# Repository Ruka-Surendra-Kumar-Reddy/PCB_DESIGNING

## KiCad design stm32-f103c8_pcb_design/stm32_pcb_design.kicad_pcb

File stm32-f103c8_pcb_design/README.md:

THIS FILE CONTAINS THE FOLLOWING :-  

schematic file of stm32f103c8  
board layout of stm32f103c8  
gerbers  
components list

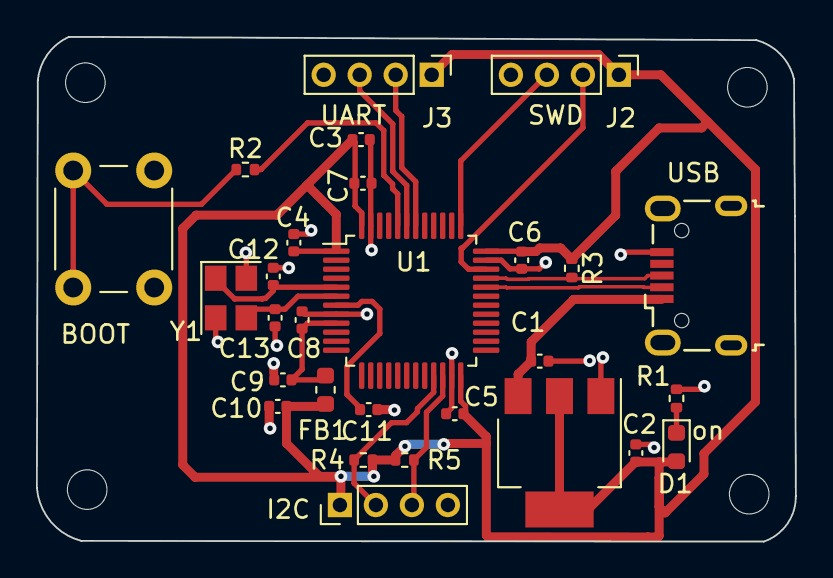
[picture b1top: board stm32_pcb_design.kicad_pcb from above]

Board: 2 copper layers, 42.2 x 28.0 mm, 32 parts (0 on the bottom side), 18 nets.

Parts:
C1, C2: 22u; C_0402_1005Metric
C3, C8: 10u; C_0402_1005Metric
C4, C5, C6, C7, C11: 100n; C_0402_1005Metric
C9, C10: 1u; C_0402_1005Metric
C12, C13: 10p; C_0402_1005Metric
D1: RED; LED_0603_1608Metric
FB1: 120R; L_0603_1608Metric
H1, H2, H3, H4: MountingHole; MountingHole_2.2mm_M2
J1: USB_B_Micro; USB_Micro-B_Wuerth_629105150521
J2, J3, J4: Conn_01x04_Pin; PinHeader_1x04_P2.00mm_Vertical
R1, R3, R4, R5: 1k5; R_0402_1005Metric
R2: 10k; R_0402_1005Metric
SW1: SW_SPDT; SW_PUSH_6mm
U1: STM32F103C8; LQFP-48_7x7mm_P0.5mm
U2: AMS1117-3.3; SOT-223-3_TabPin2
Y1: 16MHZ; Crystal_SMD_3225-4Pin_3.2x2.5mm

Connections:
+3.3V: C2.1, C3.1, C4.1, C5.1, C6.1, C7.1, C10.1, D1.2 (A), FB1.2, J2.1, J3.1, J4.1, R3.1, R4.1, R5.1, U1.1 (VBAT), U1.24 (VDD), U1.36 (VDD), U1.48 (VDD), U2.2 (VO)
+3.3VA: C8.1, C9.1, FB1.1, U1.9 (VDDA)
/BOOTO: R2.2, U1.44 (BOOT0)
/HSE_IN: C12.1, U1.5 (PD0), Y1.1
/HSE_OUT: C13.1, U1.6 (PD1), Y1.3
/I2C_SCL: J4.2, R4.2, U1.21 (PB10)
/I2C_SDA: J4.3, R5.2, U1.22 (PB11)
/NRST: C11.1, U1.7 (NRST)
/PWR_LED_K: D1.1 (K), R1.1
/SWCLK: J2.3, U1.37 (PA14)
/SWDIO: J2.2, U1.34 (PA13)
/SW_BOOTO: R2.1, SW1.2 (B)
/USART1_RX: J3.3, U1.43 (PB7)
/USART1_TX: J3.2, U1.42 (PB6)
/USB_D+: J1.3 (D+), R3.2, U1.33 (PA12)
/USB_D-: J1.2 (D-), U1.32 (PA11)
GND: C1.2, C2.2, C3.2, C4.2, C5.2, C6.2, C7.2, C8.2, C9.2, C10.2, C11.2, C12.2, C13.2, J1.5 (GND), J2.4, J3.4, J4.4, R1.2, SW1.1 (A), U1.8 (VSSA), U1.23 (VSS), U1.35 (VSS), U1.47 (VSS), U2.1 (GND), Y1.2, Y1.4
VBUS: C1.1, J1.1 (VBUS), U2.3 (VI)

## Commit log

2023-04-11 Create GERBERS
